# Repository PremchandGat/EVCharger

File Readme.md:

# EVCharger Project.
## About
The purpose of this project is to create Smart EV-Charger that has the features as following.
1. Prepaid billing system.
2. Single-phase metering.
3. Real-time charging usage track on the Android app. 
4. Charging and usage history.
5. Charger is accessible by scanning the QR code on the app.
6. Charger is accessible via RFID.
7. Dashboard to monitor the charging station's status.

## Dependencies
We are creating whole project in multiple modules as following- 
1. Power Supply
2. Microcontroller
3. Metering

### Hardware Dependency
### Power Supply
1. Transformer
2. Diode
3. Capacitor
4. LM7805
### Microcontroller
1. ESP32-WROOM32 => Microcontroller chip
2. AMS1117 => 3.3Volt regulator
3. Resistor => 4700ohm,12Kohm,330ohm
4. Capacitor => 10uf, 100nf
4. Push button => Button
5. LED
### Metering
1. ADE9153A
2. WSK12161L000FEA (Shunt Resistor)
3. LED
4. Capacitors
    1. 4.7uF (9  Quantity)
    2. 0.1uf (9  Quantity)
    3. 0.47uf (1  Quantity)
    4. 0.15uF (1 Quantity)
    5. 22pF (2 Quantity)
    7. 100nF (6 Quantity)
    8. 1uF (1 Quantity)
5. Resistor
    1. 150Ω (2 Quantity)
    2. 1kΩ (1 Quantity)
    3. 330kΩ (3 Quantity)
    5. 250KΩ (4 Quantity)
    6. 10KΩ (2 Quantity)
7. Oscillator 12.288MHz
    1. Operating temperature: −40°C to +85°C
    2. Frequency tolerance: ≤ ±50 ppm
    3. Frequency stability: ≤ ±30 ppm

### Other modules
1. I2C
2. LCD 16*2

### Software Dependency
1. Eagle
2. VS-Code
3. Flutter
4. Android Studio
5. Node.Js
6. MySQL

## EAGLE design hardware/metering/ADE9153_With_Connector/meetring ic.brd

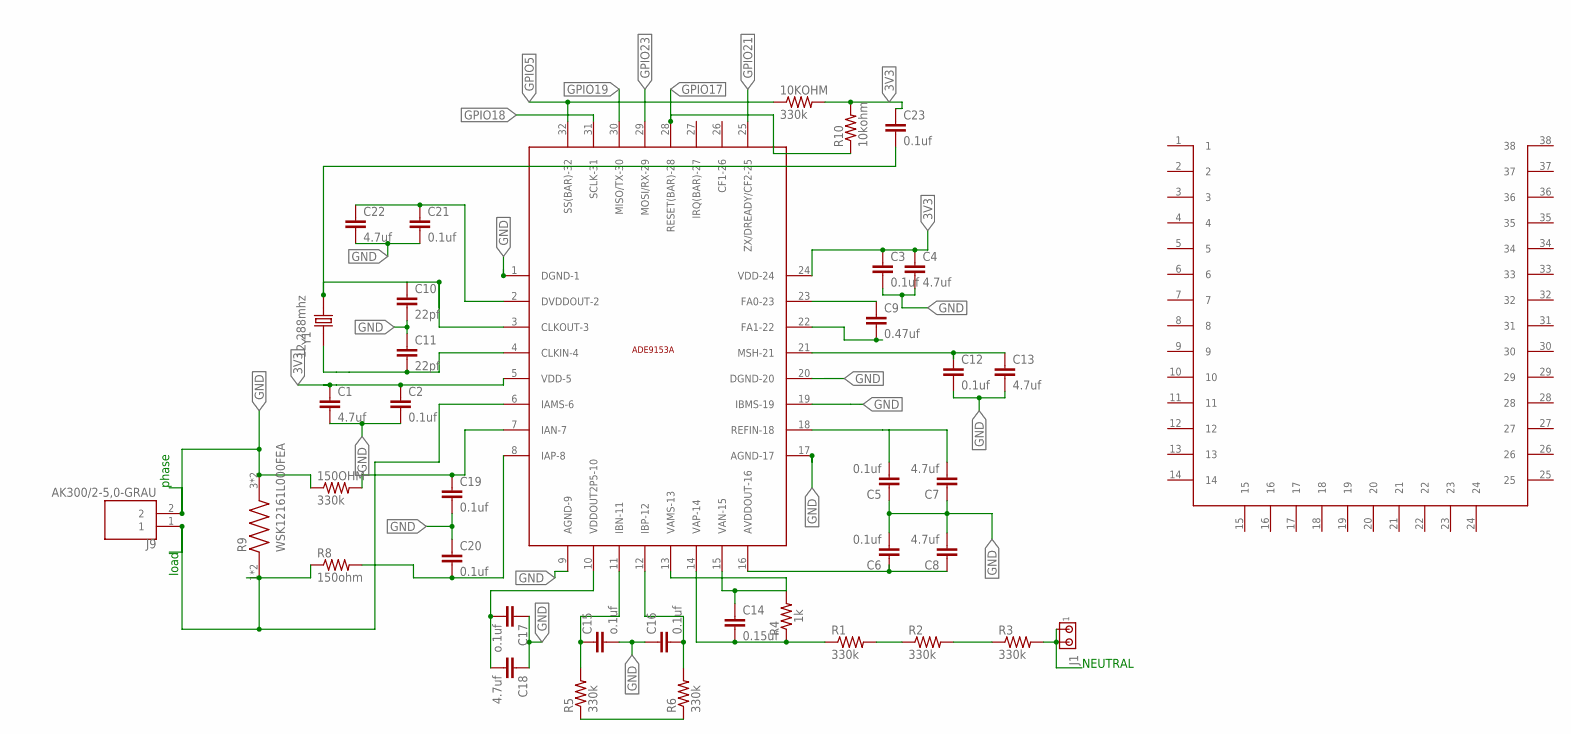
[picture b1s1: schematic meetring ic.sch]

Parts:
10KOHM, 150OHM: 330k; 0204/7
C1, C4, C7, C8, C13, C18, C22: 4.7uf; C2.5-2
C2, C3, C5, C6, C12, C16, C19, C20, C21, C23: 0.1uf; C2.5-2
C9: 0.47uf; C2.5-2
C10, C11: 22pf; C2.5-2
C14: 0.15uf; C2.5-2
C15, C17: o.1uf; C2.5-2
J1: MTA02-156; 1X2MTA
J9: AK300/2-5,0-GRAU; PTR_AK300/2-5,0-GRAU
R1, R2, R3, R5, R6: 330k; 0204/7
R4: 1k; 0204/7
R8: 150ohm; 0204/7
R9: WSK12161L000FEA; RES_WSK12161L000FEA
R10: 10kohm; 0204/7
U$1: ADE9153A_BASEADE9153A_BASE; ADE9153A_BASE
U$2: LIB1OPTION_HOLE; 1X14MTA
Y1: 12.288mhz; XTAL_ECS-200-20-1X

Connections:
3V3: 10KOHM.2, C1.1, C2.1, C3.1, C4.1, C23.1, R10.2, U$1.5 (VDD-5), U$1.24 (VDD-24)
GND: 150OHM.1, C1.2, C2.2, C3.2, C4.2, C5.1, C6.2, C7.1, C8.2, C10.2, C11.1, C12.2, C13.2, C15.2, C16.1, C17.1, C18.1, C19.2, C20.1, C21.2, C22.2, J9.2, R9.3 (2), R9.4 (2), U$1.1 (DGND-1), U$1.9 (AGND-9), U$1.17 (AGND-17), U$1.19 (IBMS-19), U$1.20 (DGND-20)
GPIO5: 10KOHM.1, U$1.32 (SS(BAR)-32)
GPIO17: R10.1, U$1.28 (RESET(BAR)-28)
GPIO18: U$1.31 (SCLK-31)
GPIO19: U$1.30 (MISO/TX-30)
GPIO21: U$1.25 (ZX/DREADY/CF2-25)
GPIO23: U$1.29 (MOSI/RX-29)
unnamed: C6.1, C8.1, U$1.16 (AVDDOUT-16)
unnamed: C5.2, C7.2, U$1.18 (REFIN-18)
unnamed: C9.1, U$1.23 (FA0-23)
unnamed: C9.2, U$1.22 (FA1-22)
unnamed: C11.2, U$1.4 (CLKIN-4), Y1.1
unnamed: C10.1, C23.2, U$1.3 (CLKOUT-3), Y1.2
unnamed: C12.1, C13.1, U$1.21 (MSH-21)
unnamed: C14.2, R1.1, R4.1, U$1.14 (VAP-14)
unnamed: R1.2, R2.1
unnamed: R2.2, R3.1
unnamed: C14.1, R4.2, U$1.13 (VAMS-13), U$1.15 (VAN-15)
unnamed: C16.2, R6.2, U$1.12 (IBP-12)
unnamed: C15.1, R5.2, U$1.11 (IBN-11)
unnamed: C17.2, C18.2, U$1.10 (VDDOUT2P5-10)
unnamed: R5.1, R6.1
unnamed: 150OHM.2, C19.1, U$1.7 (IAN-7)
unnamed: C20.2, R8.2, U$1.8 (IAP-8)
unnamed: C21.1, C22.1, U$1.2 (DVDDOUT-2)
unnamed: J9.1, R8.1, R9.1, R9.2 (1), U$1.6 (IAMS-6)
unnamed: J1.1, J1.2, R3.2

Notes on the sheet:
phase
load
NEUTRAL

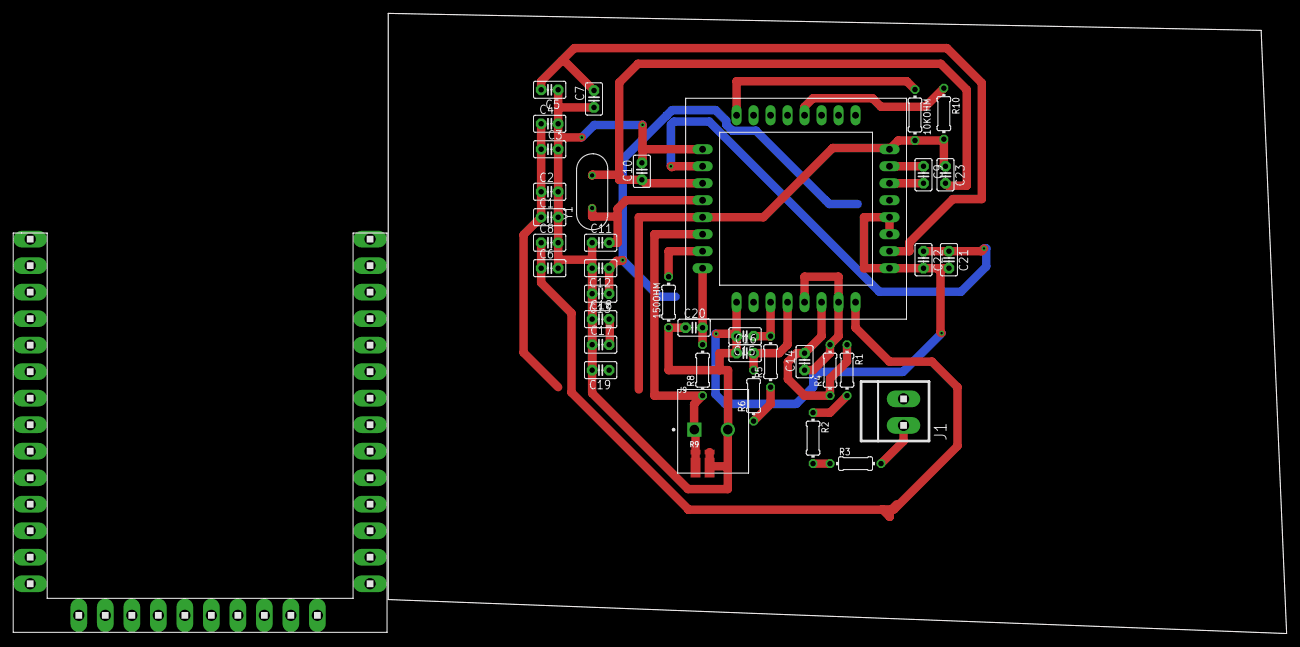
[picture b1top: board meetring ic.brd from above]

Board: 2 copper layers, 134.3 x 92.7 mm, 39 parts (0 on the bottom side), 24 nets.

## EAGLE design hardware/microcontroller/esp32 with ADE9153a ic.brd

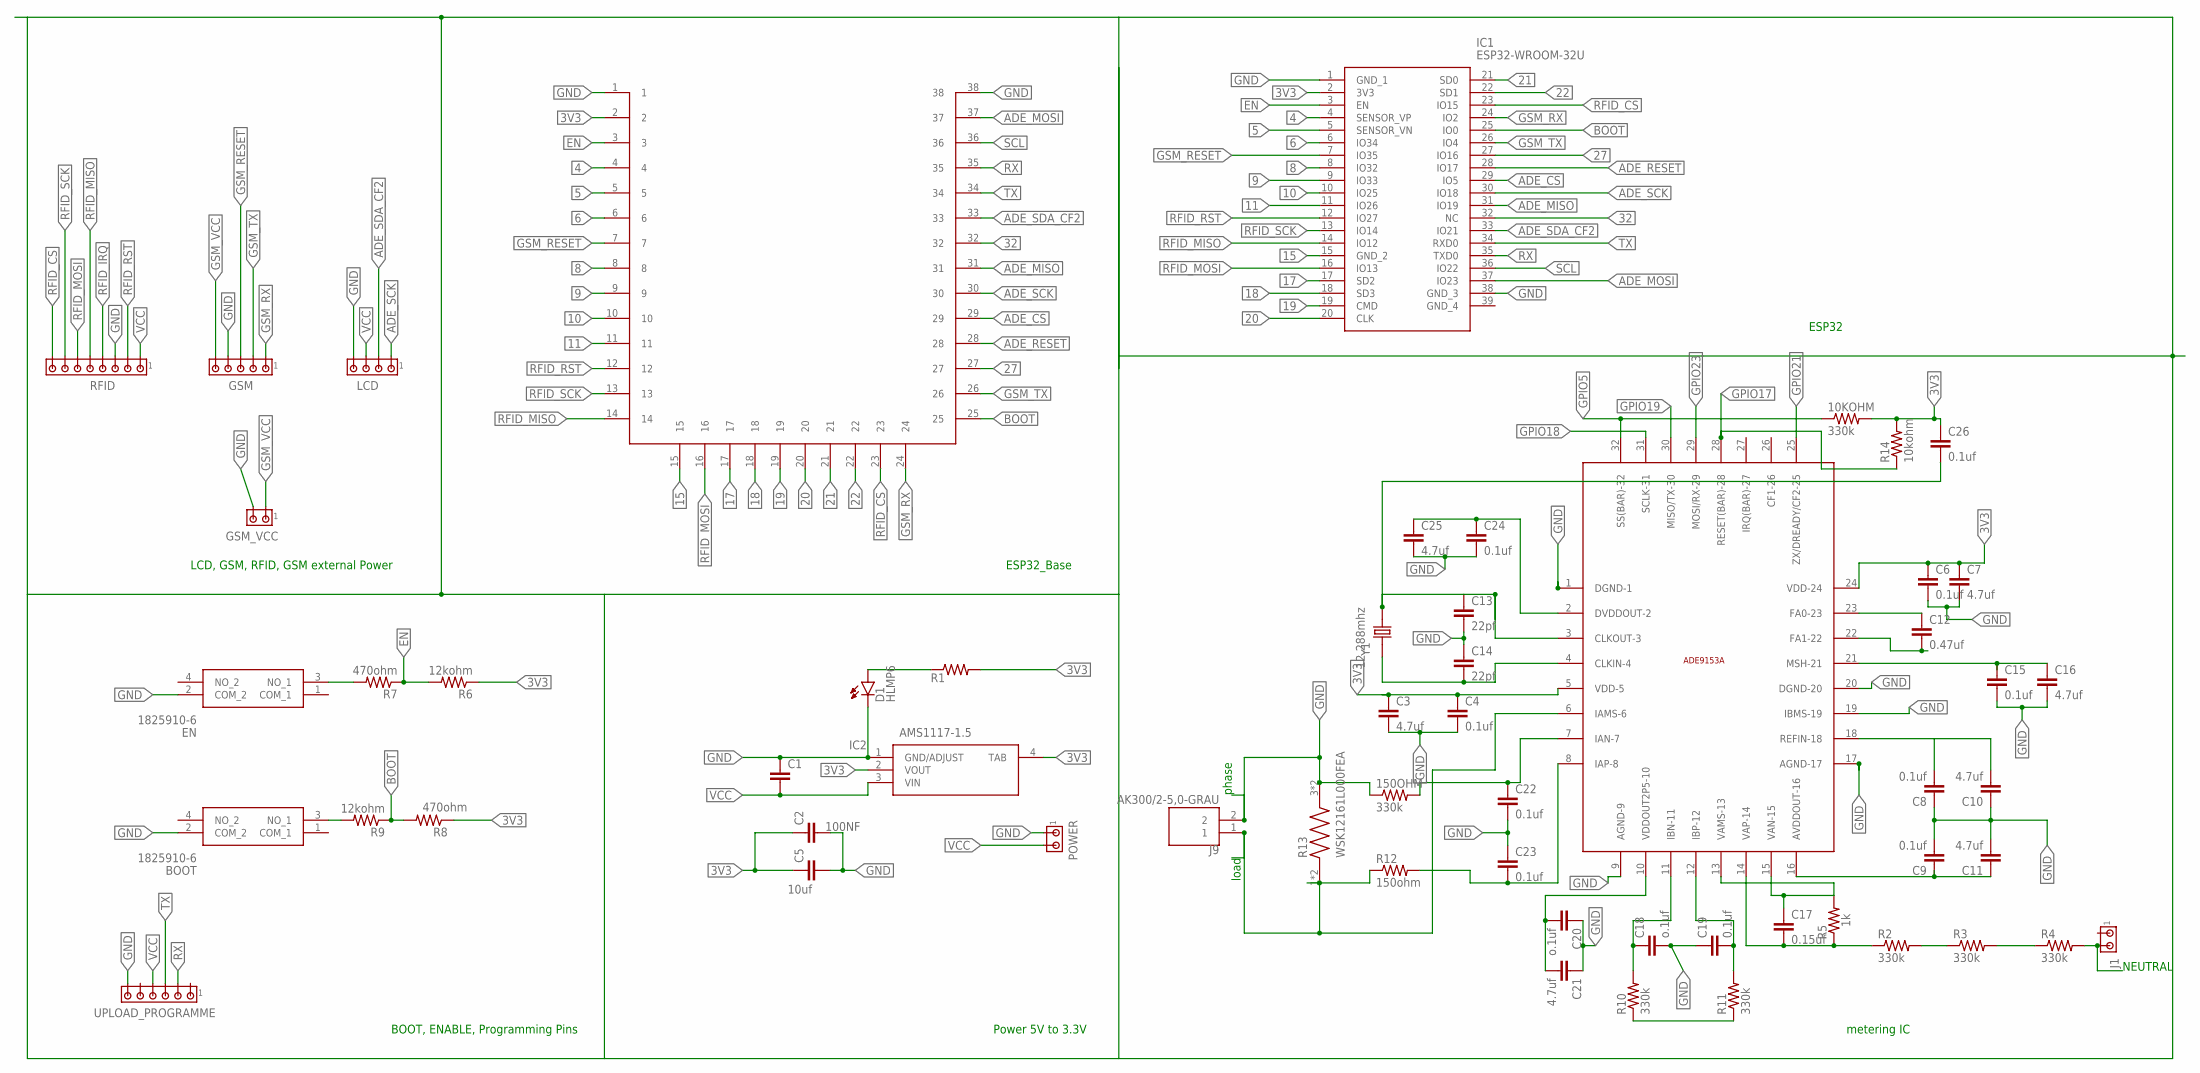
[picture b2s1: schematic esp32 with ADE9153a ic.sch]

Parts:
10KOHM, 150OHM: 330k; 0204/7
BOOT: 1825910-6; 18259106; MPN FSM4JH
C1: C2,5-3; C2.5-3
C2: 100NF; C2.5-3
C3, C7, C10, C11, C16, C21, C25: 4.7uf; C2.5-2
C4, C6, C8, C9, C15, C19, C22, C23, C24, C26: 0.1uf; C2.5-2
C5: 10uf; C2.5-3
C12: 0.47uf; C2.5-2
C13, C14: 22pf; C2.5-2
C17: 0.15uf; C2.5-2
C18, C20: o.1uf; C2.5-2
D1: HLMP6
EN: 1825910-6; 18259106; MPN FSM4JH
GSM: MTA05-156; 1X5MTA
GSM_VCC: MTA02-156; 1X2MTA
IC1: ESP32-WROOM-32U; ESP32WROOM32D
IC2: AMS1117-1.5; SOT229P700X180-4N
J1: MTA02-156; 1X2MTA
J9: AK300/2-5,0-GRAU; PTR_AK300/2-5,0-GRAU
LCD: MTA04-156; 1X4MTA
POWER: MTA02-156; 1X2MTA
R1: R-US_0204/7; 0204/7
R2, R3, R4, R10, R11: 330k; 0204/7
R5: 1k; 0204/7
R6, R9: 12kohm; RESC2012X65N
R7, R8: 470ohm; RESC2012X65N
R12: 150ohm; 0204/7
R13: WSK12161L000FEA; RES_WSK12161L000FEA
R14: 10kohm; 0204/7
RFID: MTA08-156; 1X8MTA
U$1: LIB1SHIV_KUMAR; 1X14MTA
U$2: ADE9153A_BASEADE9153A_BASE; ADE9153A_BASE
UPLOAD_PROGRAMME: MTA06-156; 1X6MTA
Y1: 12.288mhz; XTAL_ECS-200-20-1X

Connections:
3V3: 10KOHM.2, C2.1, C3.1, C4.1, C5.1, C6.1, C7.1, C26.1, IC1.2 (3V3), IC2.2 (VOUT), IC2.4 (TAB), R1.2, R6.1, R8.1, R14.2, U$1.2, U$2.5 (VDD-5), U$2.24 (VDD-24)
4: IC1.4 (SENSOR_VP), U$1.4
5: IC1.5 (SENSOR_VN), U$1.5
6: IC1.6 (IO34), U$1.6
8: IC1.8 (IO32), U$1.8
9: IC1.9 (IO33), U$1.9
10: IC1.10 (IO25), U$1.10
11: IC1.11 (IO26), U$1.11
15: IC1.15 (GND_2), U$1.15
17: IC1.17 (SD2), U$1.17
18: IC1.18 (SD3), U$1.18
19: IC1.19 (CMD), U$1.19
20: IC1.20 (CLK), U$1.20
21: IC1.21 (SD0), U$1.21
22: IC1.22 (SD1), U$1.22
27: IC1.27 (IO16), U$1.27
32: IC1.32 (NC), U$1.32
ADE_CS: IC1.29 (IO5), U$1.29
ADE_MISO: IC1.31 (IO19), U$1.31
ADE_MOSI: IC1.37 (IO23), U$1.37
ADE_RESET: IC1.28 (IO17), U$1.28
ADE_SCK: IC1.30 (IO18), LCD.1, U$1.30
ADE_SDA_CF2: IC1.33 (IO21), LCD.2, U$1.33
BOOT: IC1.25 (IO0), R8.2, R9.1, U$1.25
EN: IC1.3 (EN), R6.2, R7.1, U$1.3
GND: 150OHM.1, BOOT.2 (COM_2), C1.1, C2.2, C3.2, C4.2, C5.2, C6.2, C7.2, C8.1, C9.2, C10.1, C11.2, C13.2, C14.1, C15.2, C16.2, C18.2, C19.1, C20.1, C21.1, C22.2, C23.1, C24.2, C25.2, D1.K, EN.2 (COM_2), GSM.4, GSM_VCC.2, IC1.1 (GND_1), IC1.38 (GND_3), IC2.1 (GND/ADJUST), J9.2, LCD.4, POWER.1, R13.3 (2), R13.4 (2), RFID.3, U$1.1, U$1.38, U$2.1 (DGND-1), U$2.9 (AGND-9), U$2.17 (AGND-17), U$2.19 (IBMS-19), U$2.20 (DGND-20), UPLOAD_PROGRAMME.6
GPIO5: 10KOHM.1, U$2.32 (SS(BAR)-32)
GPIO17: R14.1, U$2.28 (RESET(BAR)-28)
GPIO18: U$2.31 (SCLK-31)
GPIO19: U$2.30 (MISO/TX-30)
GPIO21: U$2.25 (ZX/DREADY/CF2-25)
GPIO23: U$2.29 (MOSI/RX-29)
GSM_RESET: GSM.3, IC1.7 (IO35), U$1.7
GSM_RX: GSM.1, IC1.24 (IO2), U$1.24
GSM_TX: GSM.2, IC1.26 (IO4), U$1.26
GSM_VCC: GSM.5, GSM_VCC.1
unnamed: C9.1, C11.1, U$2.16 (AVDDOUT-16)
unnamed: C8.2, C10.2, U$2.18 (REFIN-18)
unnamed: C12.1, U$2.23 (FA0-23)
unnamed: C12.2, U$2.22 (FA1-22)
unnamed: C14.2, U$2.4 (CLKIN-4), Y1.1
unnamed: C13.1, C26.2, U$2.3 (CLKOUT-3), Y1.2
unnamed: C15.1, C16.1, U$2.21 (MSH-21)
unnamed: C17.2, R2.1, R5.1, U$2.14 (VAP-14)
unnamed: R2.2, R3.1
unnamed: R3.2, R4.1
unnamed: C17.1, R5.2, U$2.13 (VAMS-13), U$2.15 (VAN-15)
unnamed: C19.2, R11.2, U$2.12 (IBP-12)
unnamed: C18.1, R10.2, U$2.11 (IBN-11)
unnamed: C20.2, C21.2, U$2.10 (VDDOUT2P5-10)
unnamed: R10.1, R11.1
unnamed: 150OHM.2, C22.1, U$2.7 (IAN-7)
unnamed: C23.2, R12.2, U$2.8 (IAP-8)
unnamed: C24.1, C25.1, U$2.2 (DVDDOUT-2)
unnamed: EN.3 (NO_1), R7.2
unnamed: J9.1, R12.1, R13.1, R13.2 (1), U$2.6 (IAMS-6)
unnamed: J1.2, R4.2
unnamed: BOOT.3 (NO_1), R9.2
unnamed: D1.A, R1.1
RFID_CS: IC1.23 (IO15), RFID.8, U$1.23
RFID_IRQ: RFID.4
RFID_MISO: IC1.14 (IO12), RFID.5, U$1.14
RFID_MOSI: IC1.16 (IO13), RFID.6, U$1.16
RFID_RST: IC1.12 (IO27), RFID.2, U$1.12
RFID_SCK: IC1.13 (IO14), RFID.7, U$1.13
RX: IC1.35 (TXD0), U$1.35, UPLOAD_PROGRAMME.2
SCL: IC1.36 (IO22), U$1.36
TX: IC1.34 (RXD0), U$1.34, UPLOAD_PROGRAMME.3
VCC: C1.2, IC2.3 (VIN), LCD.3, POWER.2, RFID.1, UPLOAD_PROGRAMME.4

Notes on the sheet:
ESP32_Base
ESP32
LCD, GSM, RFID, GSM external Power
Power 5V to 3.3V
BOOT, ENABLE, Programming Pins
phase
load
NEUTRAL
metering IC

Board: 2 copper layers, 58 parts (0 on the bottom side), 64 nets, no tracks yet.

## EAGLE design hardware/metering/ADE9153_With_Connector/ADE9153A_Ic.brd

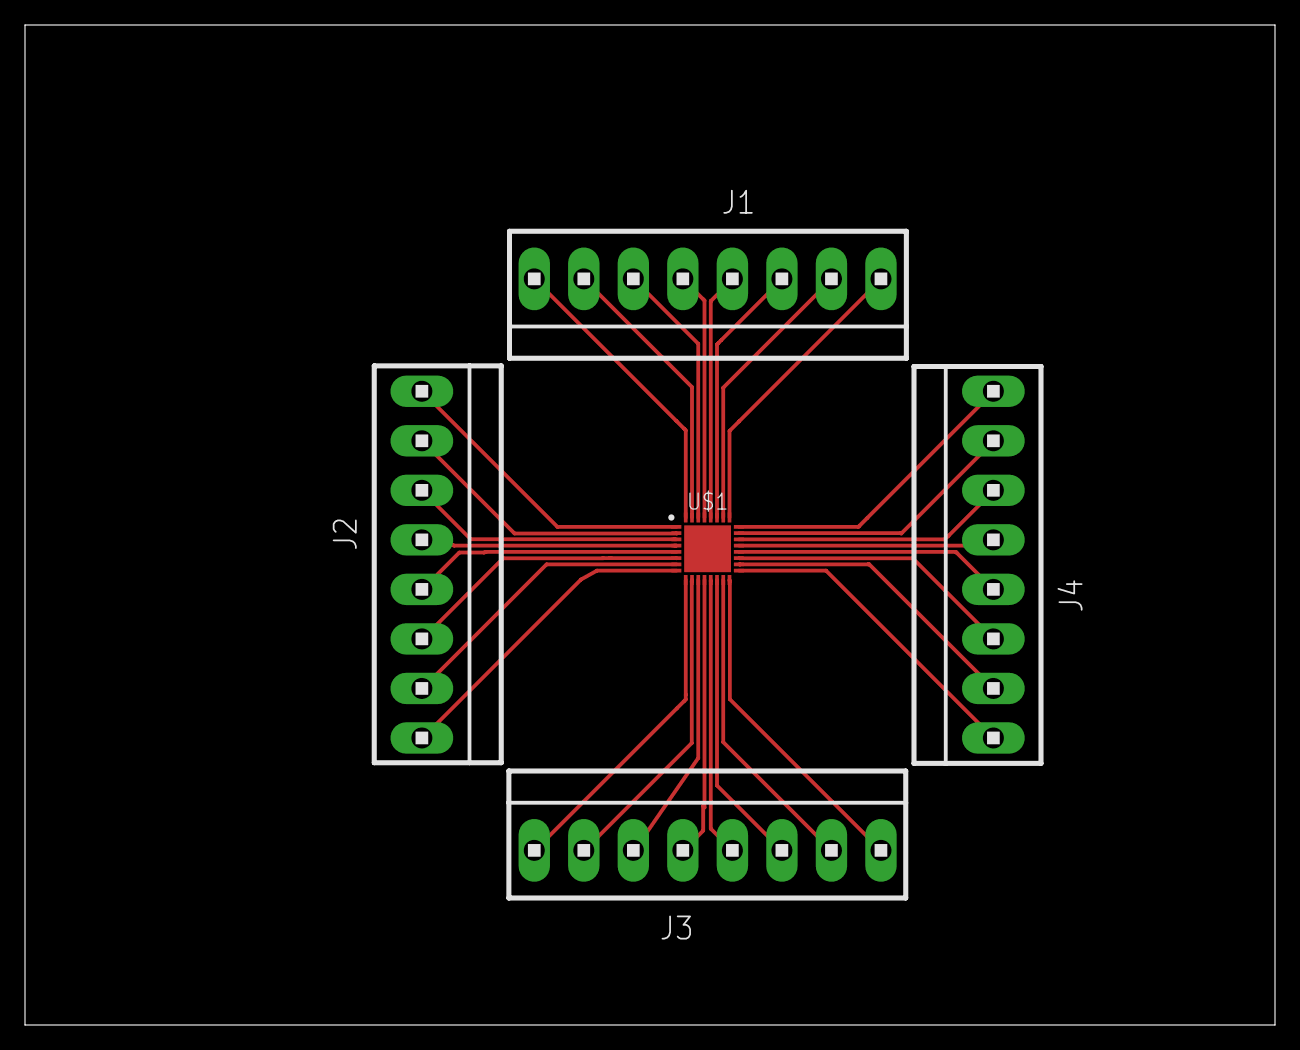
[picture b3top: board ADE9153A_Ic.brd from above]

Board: 2 copper layers, 100.0 x 80.0 mm, 5 parts (0 on the bottom side), 32 nets.

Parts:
J1, J2, J3, J4: 1X8MTA
U$1: ADE9153AACPZ; QFN50P500X500X80-33N

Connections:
1: J2.8, U$1.1
2: J2.7, U$1.2
3: J2.6, U$1.3
4: J2.5, U$1.4
5: J2.4, U$1.5
6: J2.3, U$1.6
7: J2.2, U$1.7
8: J2.1, U$1.8
9: J3.8, U$1.9
10: J3.7, U$1.10
11: J3.6, U$1.11
12: J3.5, U$1.12
13: J3.4, U$1.13
14: J3.3, U$1.14
15: J3.2, U$1.15
16: J3.1, U$1.16
17: J4.8, U$1.17
18: J4.7, U$1.18
19: J4.6, U$1.19
20: J4.5, U$1.20
21: J4.4, U$1.21
22: J4.3, U$1.22
23: J4.2, U$1.23
24: J4.1, U$1.24
25: J1.8, U$1.25
26: J1.7, U$1.26
27: J1.6, U$1.27
28: J1.5, U$1.28
29: J1.4, U$1.29
30: J1.3, U$1.30
31: J1.2, U$1.31
32: J1.1, U$1.32

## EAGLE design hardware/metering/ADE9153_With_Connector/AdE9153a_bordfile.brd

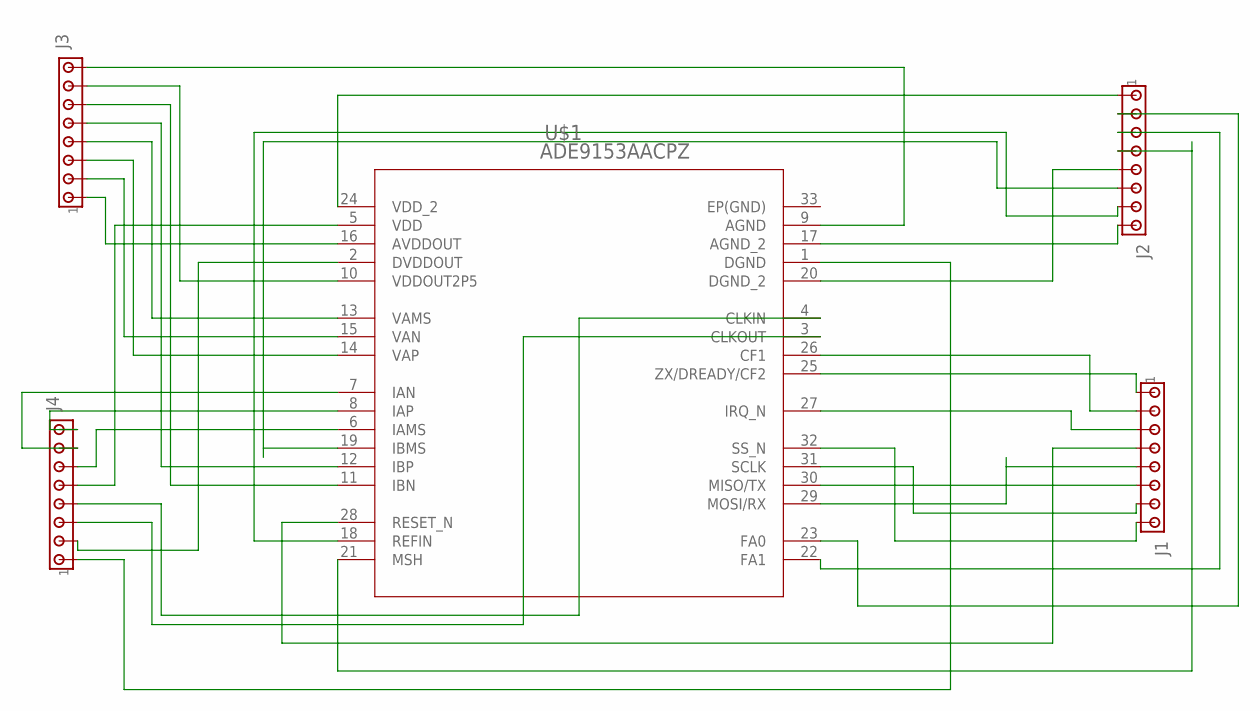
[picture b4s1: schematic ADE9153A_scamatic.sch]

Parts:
J1, J2, J3, J4: MTA08-100; 10X08MTA
U$1: ADE9153AACPZ; QFN50P500X500X80-33N

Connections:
unnamed: J1.1, U$1.25 (ZX/DREADY/CF2)
unnamed: J1.2, U$1.26 (CF1)
unnamed: J1.3, U$1.27 (IRQ_N)
unnamed: J1.4, U$1.28 (RESET_N)
unnamed: J1.5, U$1.29 (MOSI/RX)
unnamed: J1.6, U$1.30 (MISO/TX)
unnamed: J1.7, U$1.31 (SCLK)
unnamed: J1.8, U$1.32 (SS_N)
unnamed: J2.8, U$1.17 (AGND_2)
unnamed: J2.7, U$1.18 (REFIN)
unnamed: J2.6, U$1.19 (IBMS)
unnamed: J2.5, U$1.20 (DGND_2)
unnamed: J2.4, U$1.21 (MSH)
unnamed: J2.3, U$1.22 (FA1)
unnamed: J2.2, U$1.23 (FA0)
unnamed: J2.1, U$1.24 (VDD_2)
unnamed: J3.8, U$1.9 (AGND)
unnamed: J3.7, U$1.10 (VDDOUT2P5)
unnamed: J3.6, U$1.11 (IBN)
unnamed: J3.5, U$1.12 (IBP)
unnamed: J3.4, U$1.13 (VAMS)
unnamed: J3.3, U$1.14 (VAP)
unnamed: J3.2, U$1.15 (VAN)
unnamed: J3.1, U$1.16 (AVDDOUT)
unnamed: J4.1, U$1.1 (DGND)
unnamed: J4.2, U$1.2 (DVDDOUT)
unnamed: J4.3, U$1.3 (CLKOUT)
unnamed: J4.4, U$1.4 (CLKIN)
unnamed: J4.5, U$1.5 (VDD)
unnamed: J4.6, U$1.6 (IAMS)
unnamed: J4.7, U$1.7 (IAN)
unnamed: J4.8, U$1.8 (IAP)

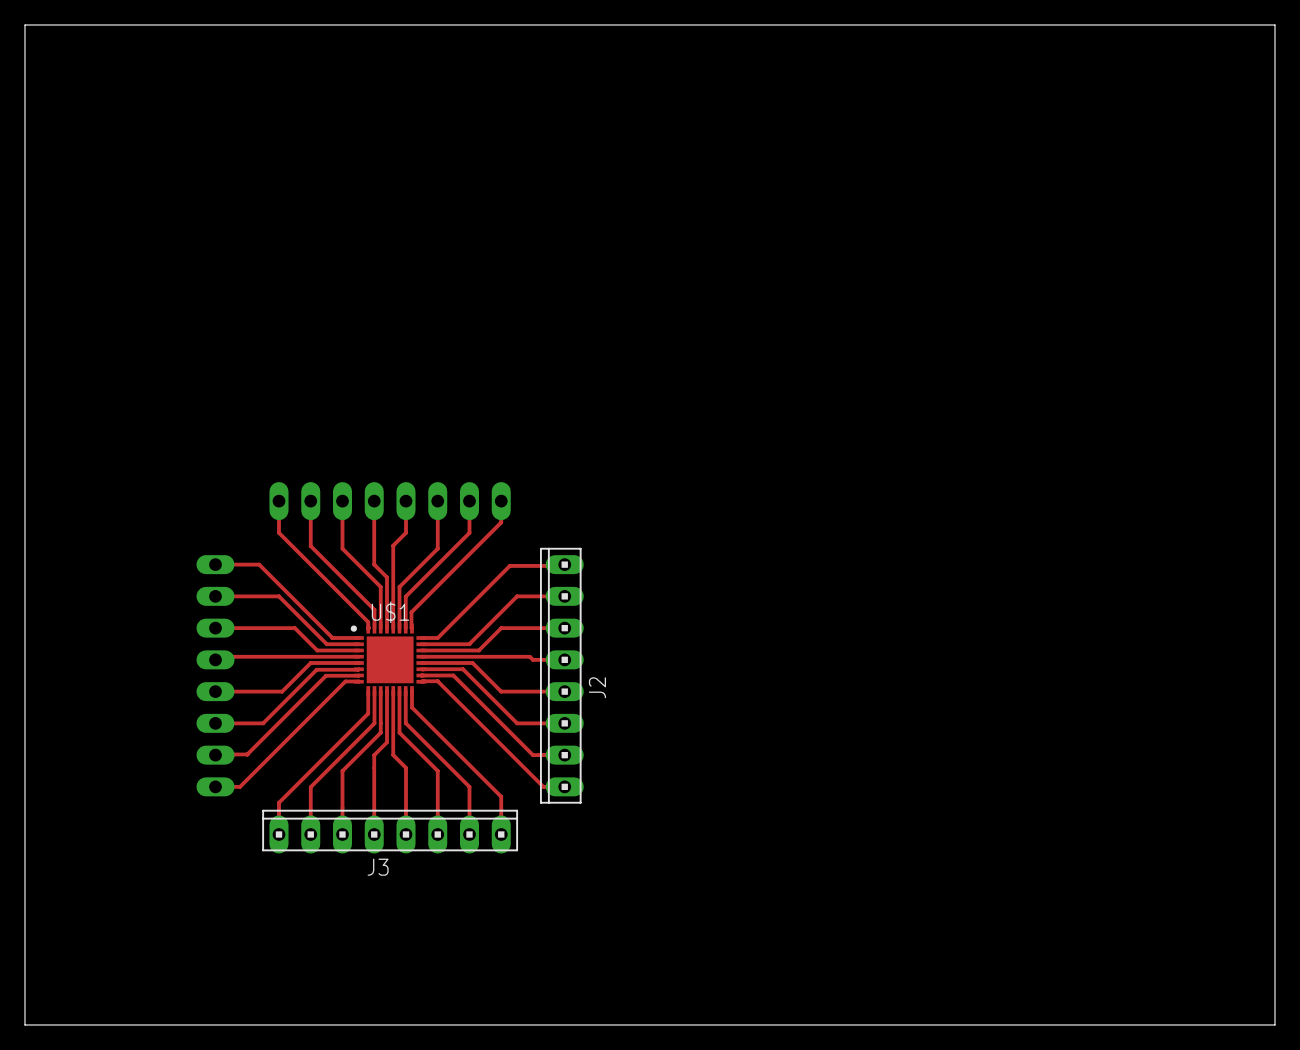
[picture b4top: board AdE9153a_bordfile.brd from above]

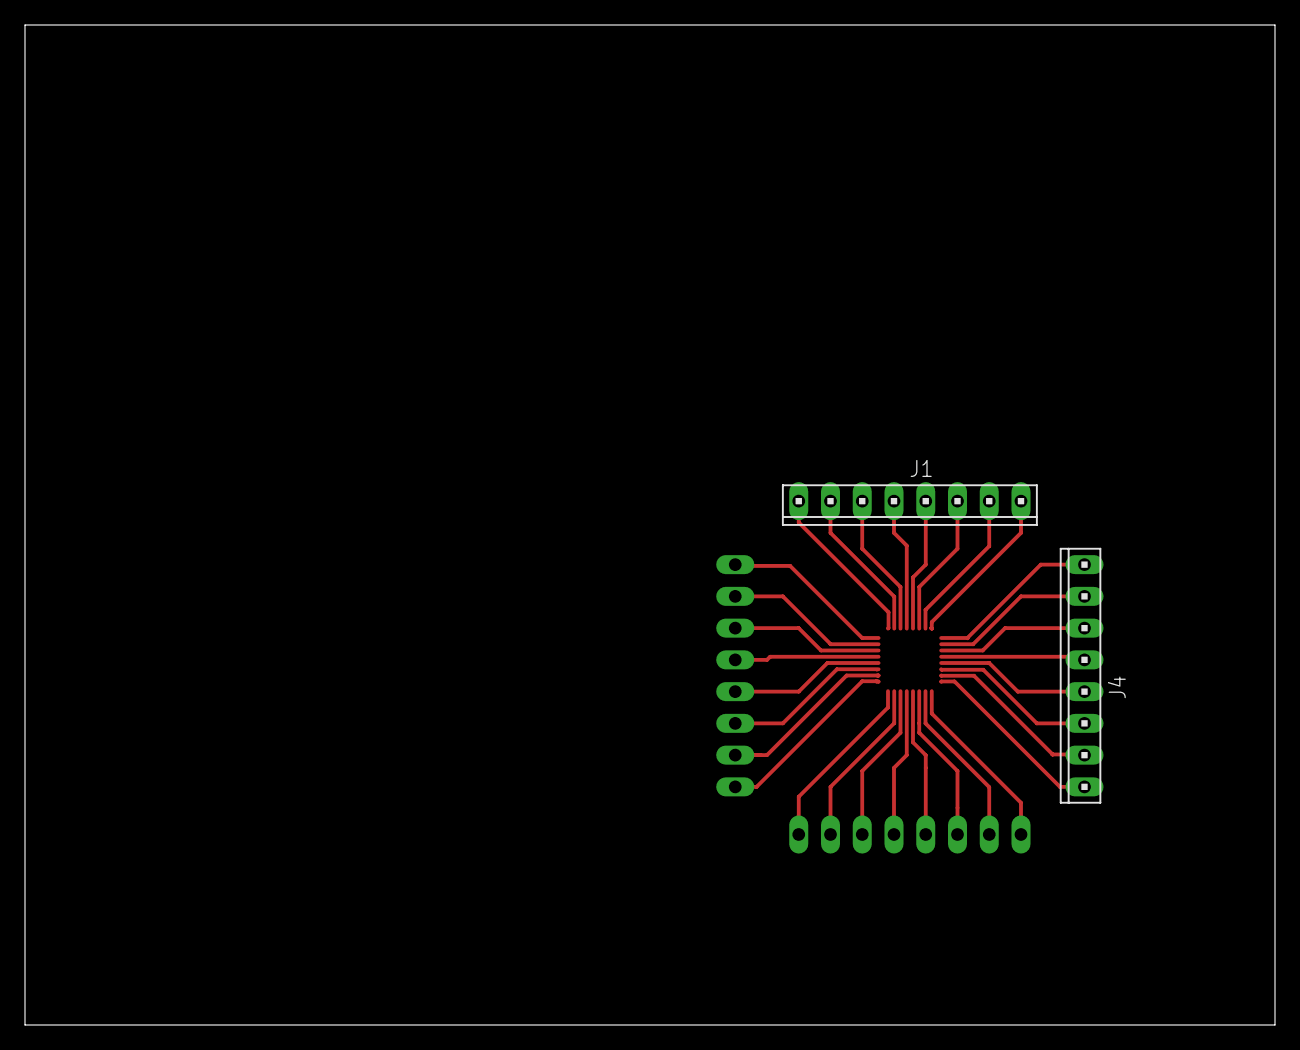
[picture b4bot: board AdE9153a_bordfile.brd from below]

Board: 2 copper layers, 100.0 x 80.0 mm, 5 parts (2 on the bottom side), 32 nets.

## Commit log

2023-04-30 Row, Column, Text, Image widgets
2023-05-01 What's App UI
2023-05-15 ADE9153 IC files
2023-05-15 Stateful
2023-05-15 TextField Learning
2023-05-16 Libraries added
2023-05-16 Readme File added
2023-05-17 scamatic and bord IC file change
2023-05-22 Pin configuration Added
2023-05-22 Readme.md
2023-05-22 ESP32_Microcontroller
2023-05-22 pin_configuration Gpio0 pin changed into Gpio17
2023-05-25 change in microcontroller disign
2023-05-25 Pin Conf
2023-05-25 Readme
2023-05-25 ESP32 Schematic clean-up
2023-05-25 ESP32 Schematic and Board Cleanup
2023-05-25 metering circuit design
2023-05-26 ESP32_design
2023-05-26 marge behind files
2023-05-26 ESP32_Final Design
2023-05-26 change in metering IC design
2023-05-30 second commit
2023-05-30 third-commit
2023-05-30 fourth-commit
2023-06-01 ADE9153Base
2023-06-01 files change
